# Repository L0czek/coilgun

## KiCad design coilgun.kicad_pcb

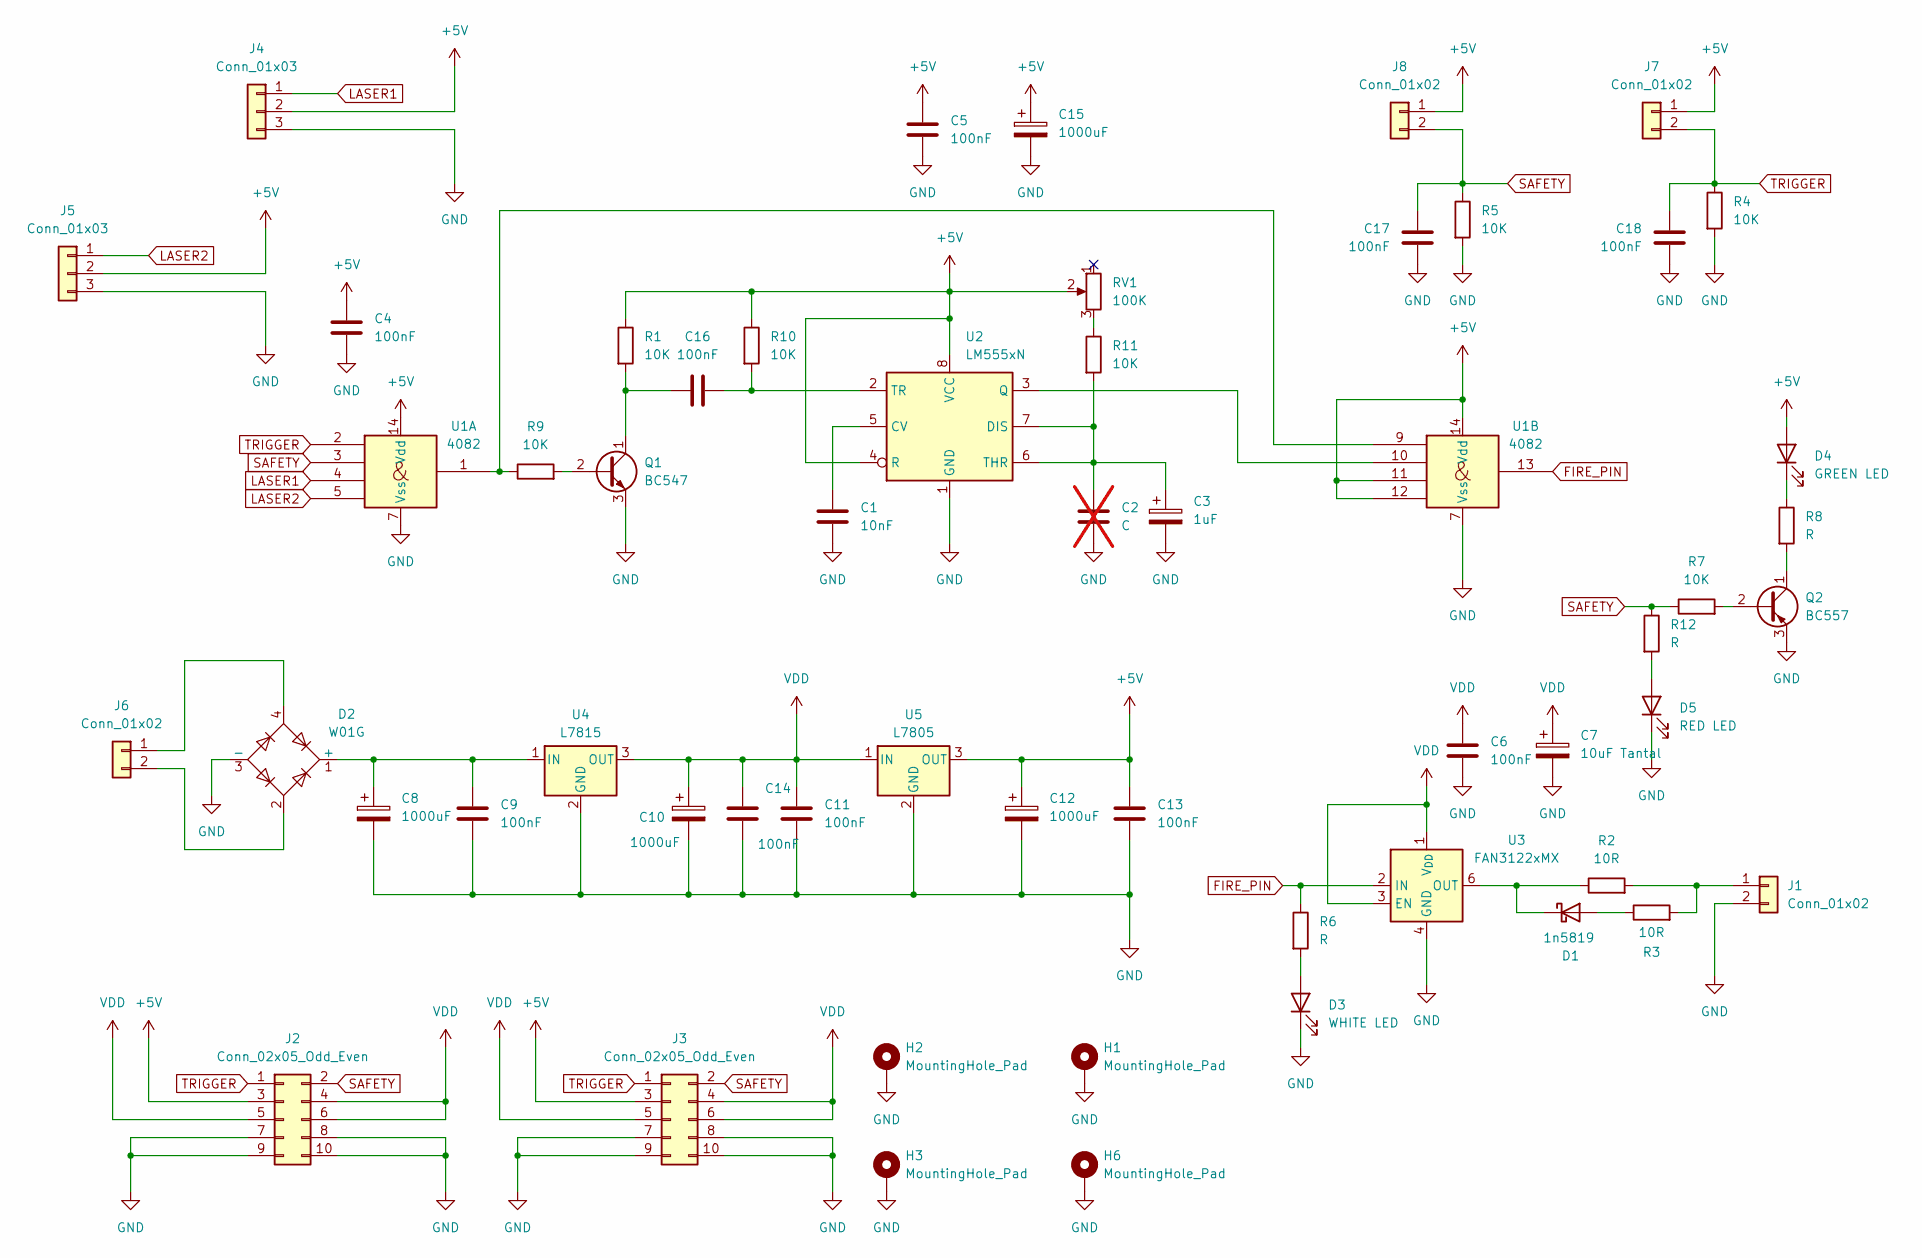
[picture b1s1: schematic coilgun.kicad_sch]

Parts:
C1: 10nF; C_Rect_L7.0mm_W2.0mm_P5.00mm
C2: C; C_Rect_L7.0mm_W2.0mm_P5.00mm; not fitted
C3: 1uF; CP_Radial_D5.0mm_P2.50mm
C4, C5, C6, C9, C11, C13, C14, C16, C17, C18: 100nF; C_Rect_L7.0mm_W2.0mm_P5.00mm
C7: 10uF Tantal; C_Rect_L7.0mm_W2.0mm_P5.00mm
C8, C10, C12, C15: 1000uF; CP_Radial_D10.0mm_P5.00mm_P7.50mm
D1: 1n5819; D_A-405_P12.70mm_Horizontal
D2: W01G; Diode_Bridge_Round_D9.8mm
D3: WHITE LED; LED_D5.0mm
D4: GREEN LED; LED_D5.0mm
D5: RED LED; LED_D5.0mm
H1, H2, H3, H6: MountingHole_Pad; MountingHole_2.2mm_M2_Pad_Via
J1, J6, J7, J8: Conn_01x02; JST_NV_B02P-NV_1x02_P5.00mm_Vertical
J2, J3: Conn_02x05_Odd_Even; IDC-Header_2x05_P2.54mm_Vertical
J4, J5: Conn_01x03; PinHeader_1x03_P2.54mm_Vertical
Q1: BC547; TO-92_HandSolder
Q2: BC557; TO-92_HandSolder
R1, R4, R5, R7, R9, R10, R11: 10K; R_Axial_DIN0309_L9.0mm_D3.2mm_P15.24mm_Horizontal
R2, R3: 10R; R_Axial_DIN0309_L9.0mm_D3.2mm_P15.24mm_Horizontal
R6, R8, R12: R; R_Axial_DIN0309_L9.0mm_D3.2mm_P15.24mm_Horizontal
RV1: 100K; Potentiometer_Bourns_3386P_Vertical
U1: 4082; CERDIP-14_W7.62mm_SideBrazed_LongPads_Socket
U2: LM555xN; DIP-8_W7.62mm_Socket_LongPads
U3: FAN3122xMX; DIP-8_W7.62mm_Socket_LongPads
U4: L7815; TO-220-3_Vertical
U5: L7805; TO-220-3_Vertical

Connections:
+5V: C4.1, C5.1, C12.1, C13.1, C15.1, D4.2 (A), J2.3, J3.3, J4.2, J5.2, J7.1, J8.1, R1.1, R10.1, RV1.2, U1.11, U1.12, U1.14 (Vdd), U2.4 (R), U2.8 (VCC), U5.3 (OUT)
FIRE_PIN: R6.1, U1.13, U3.2 (IN)
GND: C1.2, C2.2, C3.2, C4.2, C5.2, C6.2, C7.2, C8.2, C9.2, C10.2, C11.2, C12.2, C13.2, C14.2, C15.2, C17.2, C18.2, D2.3 (-), D3.1 (K), D5.1 (K), H1.1 (1_1), H2.1 (1_1), H3.1 (1_1), H6.1 (1_1), J1.2, J2.7, J2.8, J2.9, J2.10, J3.7, J3.8, J3.9, J3.10, J4.3, J5.3, Q1.3 (E), Q2.3 (E), R4.2, R5.2, U1.7 (Vss), U2.1 (GND), U3.4 (GND), U3.5 (GND), U4.2 (GND), U5.2 (GND)
LASER1: J4.1, U1.4
LASER2: J5.1, U1.5
unnamed: D1.2 (A), R3.1
unnamed: D1.1 (K), R2.1, U3.6 (OUT), U3.7 (OUT)
unnamed: C8.1, C9.1, D2.1 (+), U4.1 (IN)
unnamed: D3.2 (A), R6.2
unnamed: D4.1 (K), R8.1
unnamed: D5.2 (A), R12.2
unnamed: J1.1, R2.2, R3.2
unnamed: D2.4, J6.1
unnamed: D2.2, J6.2
unnamed: Q1.2 (B), R9.2
unnamed: C16.1, Q1.1 (C), R1.2
unnamed: Q2.2 (B), R7.2
unnamed: Q2.1 (C), R8.2
unnamed: R9.1, U1.1, U1.9
unnamed: R11.1, RV1.3
unnamed: C1.1, U2.5 (CV)
unnamed: C2.1, C3.1, R11.2, U2.6 (THR), U2.7 (DIS)
unnamed: U1.10, U2.3 (Q)
unnamed: C16.2, R10.2, U2.2 (TR)
SAFETY: C17.1, J2.2, J3.2, J8.2, R5.1, R7.1, R12.1, U1.3
TRIGGER: C18.1, J2.1, J3.1, J7.2, R4.1, U1.2
VDD: C6.1, C7.1, C10.1, C11.1, C14.1, J2.4, J2.5, J2.6, J3.4, J3.5, J3.6, U3.1 (V_{DD}), U3.3 (EN), U3.8 (V_{DD}), U4.3 (OUT), U5.1 (IN)

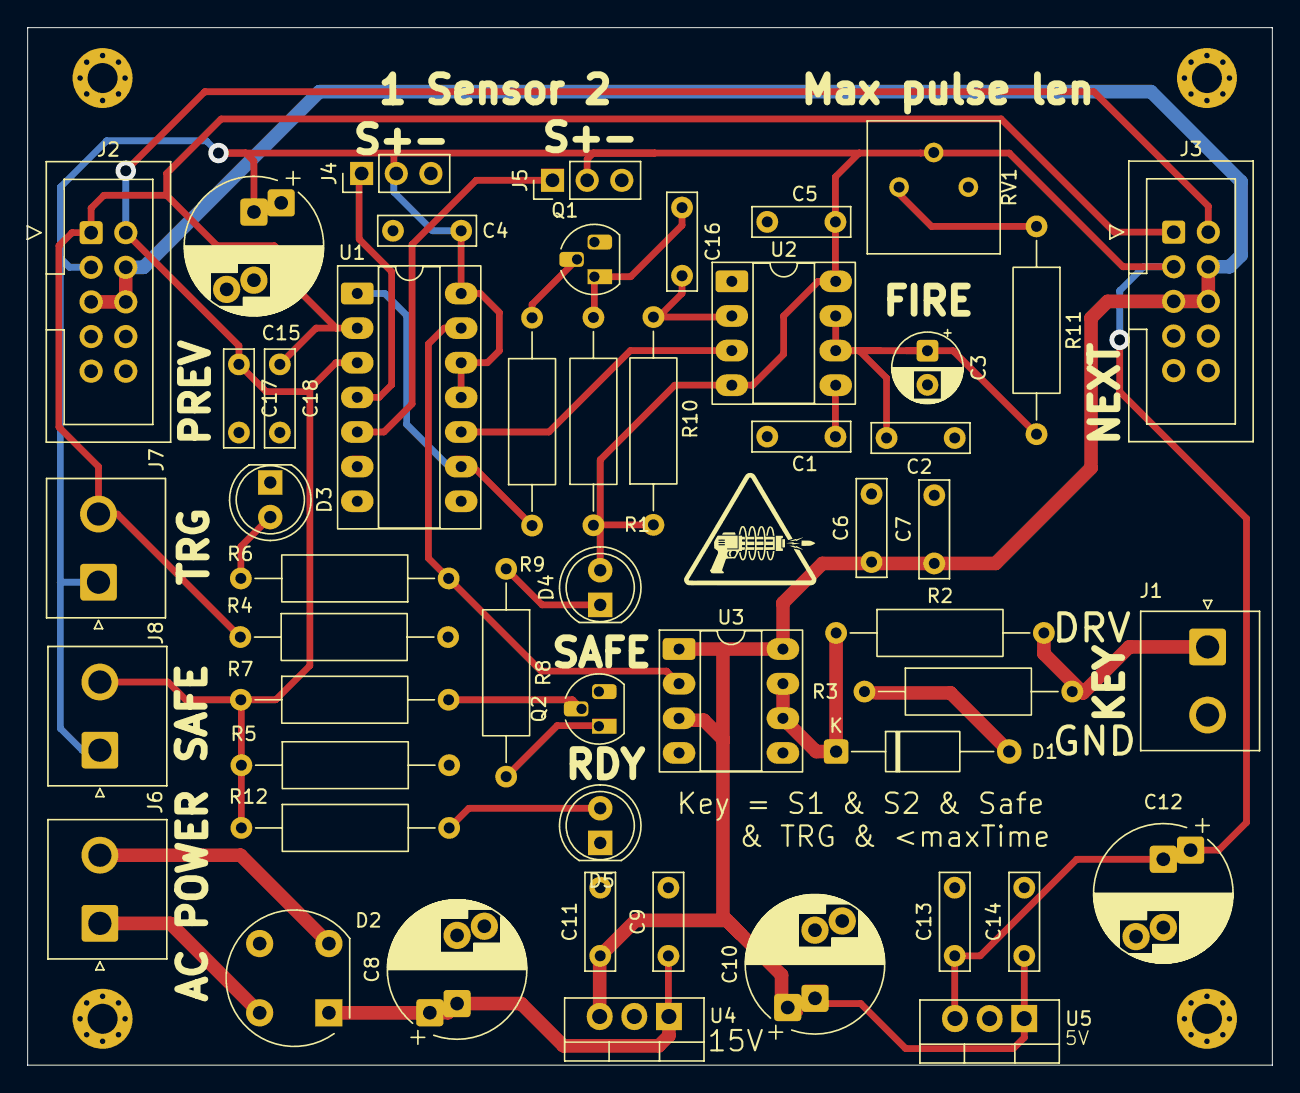
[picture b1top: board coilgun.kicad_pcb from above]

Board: 2 copper layers, 91.3 x 76.1 mm, 55 parts (0 on the bottom side), 27 nets.

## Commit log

2025-12-03 Add schematic
2025-12-03 Route pcb
2025-12-03 Add values to elements
2025-12-03 Add schematic in pdf
2025-12-06 Fix bugs and label placement
2025-12-08 Release 08.12.2025
2026-05-14 Fix error
2026-05-16 safe led, fix 555 trigger, logos
2026-05-21 text update
2026-05-23 Plot
